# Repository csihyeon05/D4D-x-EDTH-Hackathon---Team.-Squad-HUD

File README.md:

# Squad HUD

Squad HUD is the open-source firmware, hardware and software for a real-time physiological monitoring and situational awareness system developed by **Team Squad HUD** for the **D4D × EDTH Hackathon 2026**.

The system uses **wearable sensor nodes** to collect physiological and motion data, a **NU40 wireless gateway** to receive sensor telemetry, and a **Common Operational Picture (COP)** to display the condition and location of connected personnel. A Python backend processes incoming packets, maintains individual personnel states, associates GPS coordinates with sensor IDs, and provides live information to the dashboard.

The repository holds the components of the system:

- **Soldier firmware** — Embedded firmware for wearable sensor nodes. Supports MPU6050 and NU-IMU configurations, collects sensor measurements and transmits compact telemetry advertisements. The integrated firmware uses an 18-byte packet format with an approximately 1 Hz update rate.
- **NU40 gateway** — Receives wireless advertisements from the sensor nodes and forwards telemetry to the command computer through a serial connection.
- **C2 backend** — Python service that decodes incoming packets, tracks personnel states, integrates GPS coordinates, handles missing measurements and detects communication timeouts.
- **Common Operational Picture (COP)** — An Angular web dashboard that displays physiological measurements, personnel locations, communication status and individual sensor availability.
- **Hardware** — PCB design files and embedded hardware configurations for the sensor and communication system.
- **Testing** — Automated backend tests, firmware tests, protocol compatibility checks and simulated telemetry for integration verification.

## System architecture

```text
┌───────────────────────────────┐
│      Wearable Sensor Node     │
│                               │
│  Physiological Sensors        │
│  MPU6050 / NU-IMU             │
│  Embedded Firmware            │
└───────────────┬───────────────┘
                │
        Wireless Telemetry
        18-byte Advertisement
                │
                ▼
┌───────────────────────────────┐
│          NU40 Gateway         │
│                               │
│  Wireless Packet Reception    │
│  Serial Telemetry Forwarding  │
└───────────────┬───────────────┘
                │
           Serial / USB
                │
                ▼
┌───────────────────────────────┐
│           C2 Backend          │
│                               │
│  Telemetry Decoder            │
│  Personnel State Management   │
│  GPS Association              │
│  Communication Timeout        │
└───────────────┬───────────────┘
                │
              API
                │
                ▼
┌───────────────────────────────┐
│          Squad HUD COP        │
│                               │
│  Physiological Monitoring     │
│  Personnel Location           │
│  Communication Status         │
└───────────────────────────────┘

             GPS Input
                │
                ▼
           C2 Backend
```

## Telemetry and monitoring

The monitoring system maintains a separate state for each connected sensor node. Every incoming telemetry packet is decoded by the backend and associated with the corresponding soldier ID.

The integrated sensor firmware transmits an **18-byte advertisement packet**. Its format and field definitions are documented in [`docs/DATA_SPEC.md`](./docs/DATA_SPEC.md).

The backend handles incoming measurements as follows:

1. **Sensor acquisition** — The wearable firmware collects physiological and motion measurements from the connected sensors.
2. **Wireless transmission** — The sensor node broadcasts a compact telemetry advertisement approximately once per second.
3. **Gateway reception** — The NU40 gateway receives the advertisement and forwards it to the backend through the serial interface.
4. **Packet decoding** — The backend parses the packet, extracts available measurements and associates them with the corresponding soldier ID.
5. **State update** — The latest measurements are stored in the personnel state and made available to the COP.
6. **GPS integration** — Coordinates submitted through `POST /api/gps` are associated with the specified `soldier_id`.
7. **Heart-rate availability** — The COP uses `hr_display_bpm` and `hr_status` to distinguish valid heart-rate measurements from unavailable data.
8. **Communication timeout** — In serial mode, a soldier is marked `UNKNOWN` when no telemetry has been received for more than 10 seconds. The threshold can be changed through `C2_STALE_AFTER_S`.

The dashboard obtains the latest personnel information through `/api/state`.

## Tech stack

- **Sensor firmware:** Embedded C/C++, MPU6050 and NU-IMU sensor configurations
- **Wireless communication:** NU40 development platform, wireless advertisements, serial telemetry
- **Backend:** Python, REST API, pytest
- **Frontend:** Angular, TypeScript
- **Hardware design:** PCB design files
- **Testing:** pytest, firmware test scripts, protocol parity tests and simulated telemetry

## Getting started

### C2 backend

The backend is located in `tactical-c2/backend`.

Run the automated backend tests:

```bash
cd tactical-c2/backend
python -m pytest
```

For the physical NU40 gateway, configure the backend to use serial telemetry input.

```bash
C2_SOURCE=serial
C2_SERIAL_PORT=COM10
```

`COM10` was used during the October 11, 2026 hardware integration test. Replace it with the serial port assigned to the gateway on your computer.

The communication timeout can also be configured:

```bash
C2_STALE_AFTER_S=10
```

### Common Operational Picture

The Angular frontend is located in `tactical-c2/frontend`.

Install dependencies and build the application:

```bash
cd tactical-c2/frontend
npm install
npx ng build
```

The frontend supports simulated telemetry and mock mode (`?mock`) for testing without the physical sensor network.

The dashboard reads personnel information from the backend and displays the latest available measurements, location data and communication state.

### Soldier firmware

The integrated wearable sensor firmware is located in `soldier-firmware`.

Run the firmware test suite:

```bash
cd soldier-firmware
sh tools/test.sh
```

The test suite includes protocol compatibility checks against the Python reference implementation used by the backend.

The firmware uses an 18-byte advertisement format and periodically updates its transmitted measurements.

### NU40 gateway

The gateway implementation is located in `firmware/nu40-commander`.

Run the protocol compatibility tests from the repository root:

```bash
BACKEND_ROOT=tactical-c2/backend \
sh firmware/nu40-commander/test/run.sh
```

These tests verify that telemetry vectors produced by the gateway implementation can be parsed by the backend.

For physical operation, connect the NU40 gateway to the command computer and configure the backend with the appropriate serial port.

## Project structure

```text
docs/
  DATA_SPEC.md                  Telemetry packet specification
  ...                           Protocol and validation documents

firmware/
  nucode-project/               MPU6050 sensor firmware
  nucode-project-for-nucode-imu/
                                NU-IMU sensor firmware
  nu40-commander/               NU40 gateway firmware
    test/                       Gateway compatibility tests

soldier-firmware/
  test/                         Sensor firmware and parity tests
  tools/                        Firmware testing scripts

tactical-c2/
  backend/                      Python telemetry processing and API
  frontend/                     Angular Common Operational Picture
  docs/                         Integration and hardware test records

pcb/                            Hardware design files

INTEGRATION.md                  Integration history and verification
LICENSE                         Apache License 2.0
```

## Integration and testing

The firmware, gateway, backend and frontend were developed as separate components and subsequently integrated into a single monitoring system.

The integration was verified on October 11, 2026.

| Component | Verification |
|---|---|
| C2 backend | 24 pytest tests passed |
| Angular COP | Production build successful |
| Soldier firmware | Automated tests passed |
| Protocol compatibility | 3 parity tests passed |
| NU40 gateway | Backend parser compatibility verified |
| Frontend simulation | Mock and virtual serial modes verified |
| Hardware communication | Live sensor telemetry received |

### Hardware verification

A physical NU40 gateway was connected to the command computer through `COM10`, with the backend configured to receive serial telemetry.

During the integration test, the backend successfully received live telemetry from sensor node `S1` at approximately one packet per second, including heart-rate measurements.

The frontend was also tested using simulated communication interruptions. The personnel state transitioned through live, reacquiring and `UNKNOWN` states according to the configured communication timeout.

The hardware test is documented in [`tactical-c2/docs/HW_TEST_2026-10-11.md`](./tactical-c2/docs/HW_TEST_2026-10-11.md).

## Status

The C2 backend, Angular frontend, sensor firmware tests and gateway protocol compatibility checks have passed their documented integration tests.

A physical NU40 gateway has successfully delivered live telemetry to the backend. The frontend has been verified using simulated data and virtual serial communication.

The system has **not yet been fully validated as an end-to-end multi-node deployment under field conditions**. Communication reliability, physiological measurement accuracy and behavior under extended operation require further hardware testing.

## Documentation

- [`INTEGRATION.md`](./INTEGRATION.md) — Integration history and verification results
- [`docs/DATA_SPEC.md`](./docs/DATA_SPEC.md) — Telemetry packet format and field definitions
- [`tactical-c2/docs/HW_TEST_2026-10-11.md`](./tactical-c2/docs/HW_TEST_2026-10-11.md) — Hardware integration test

## License

Licensed under the [Apache License 2.0](./LICENSE).

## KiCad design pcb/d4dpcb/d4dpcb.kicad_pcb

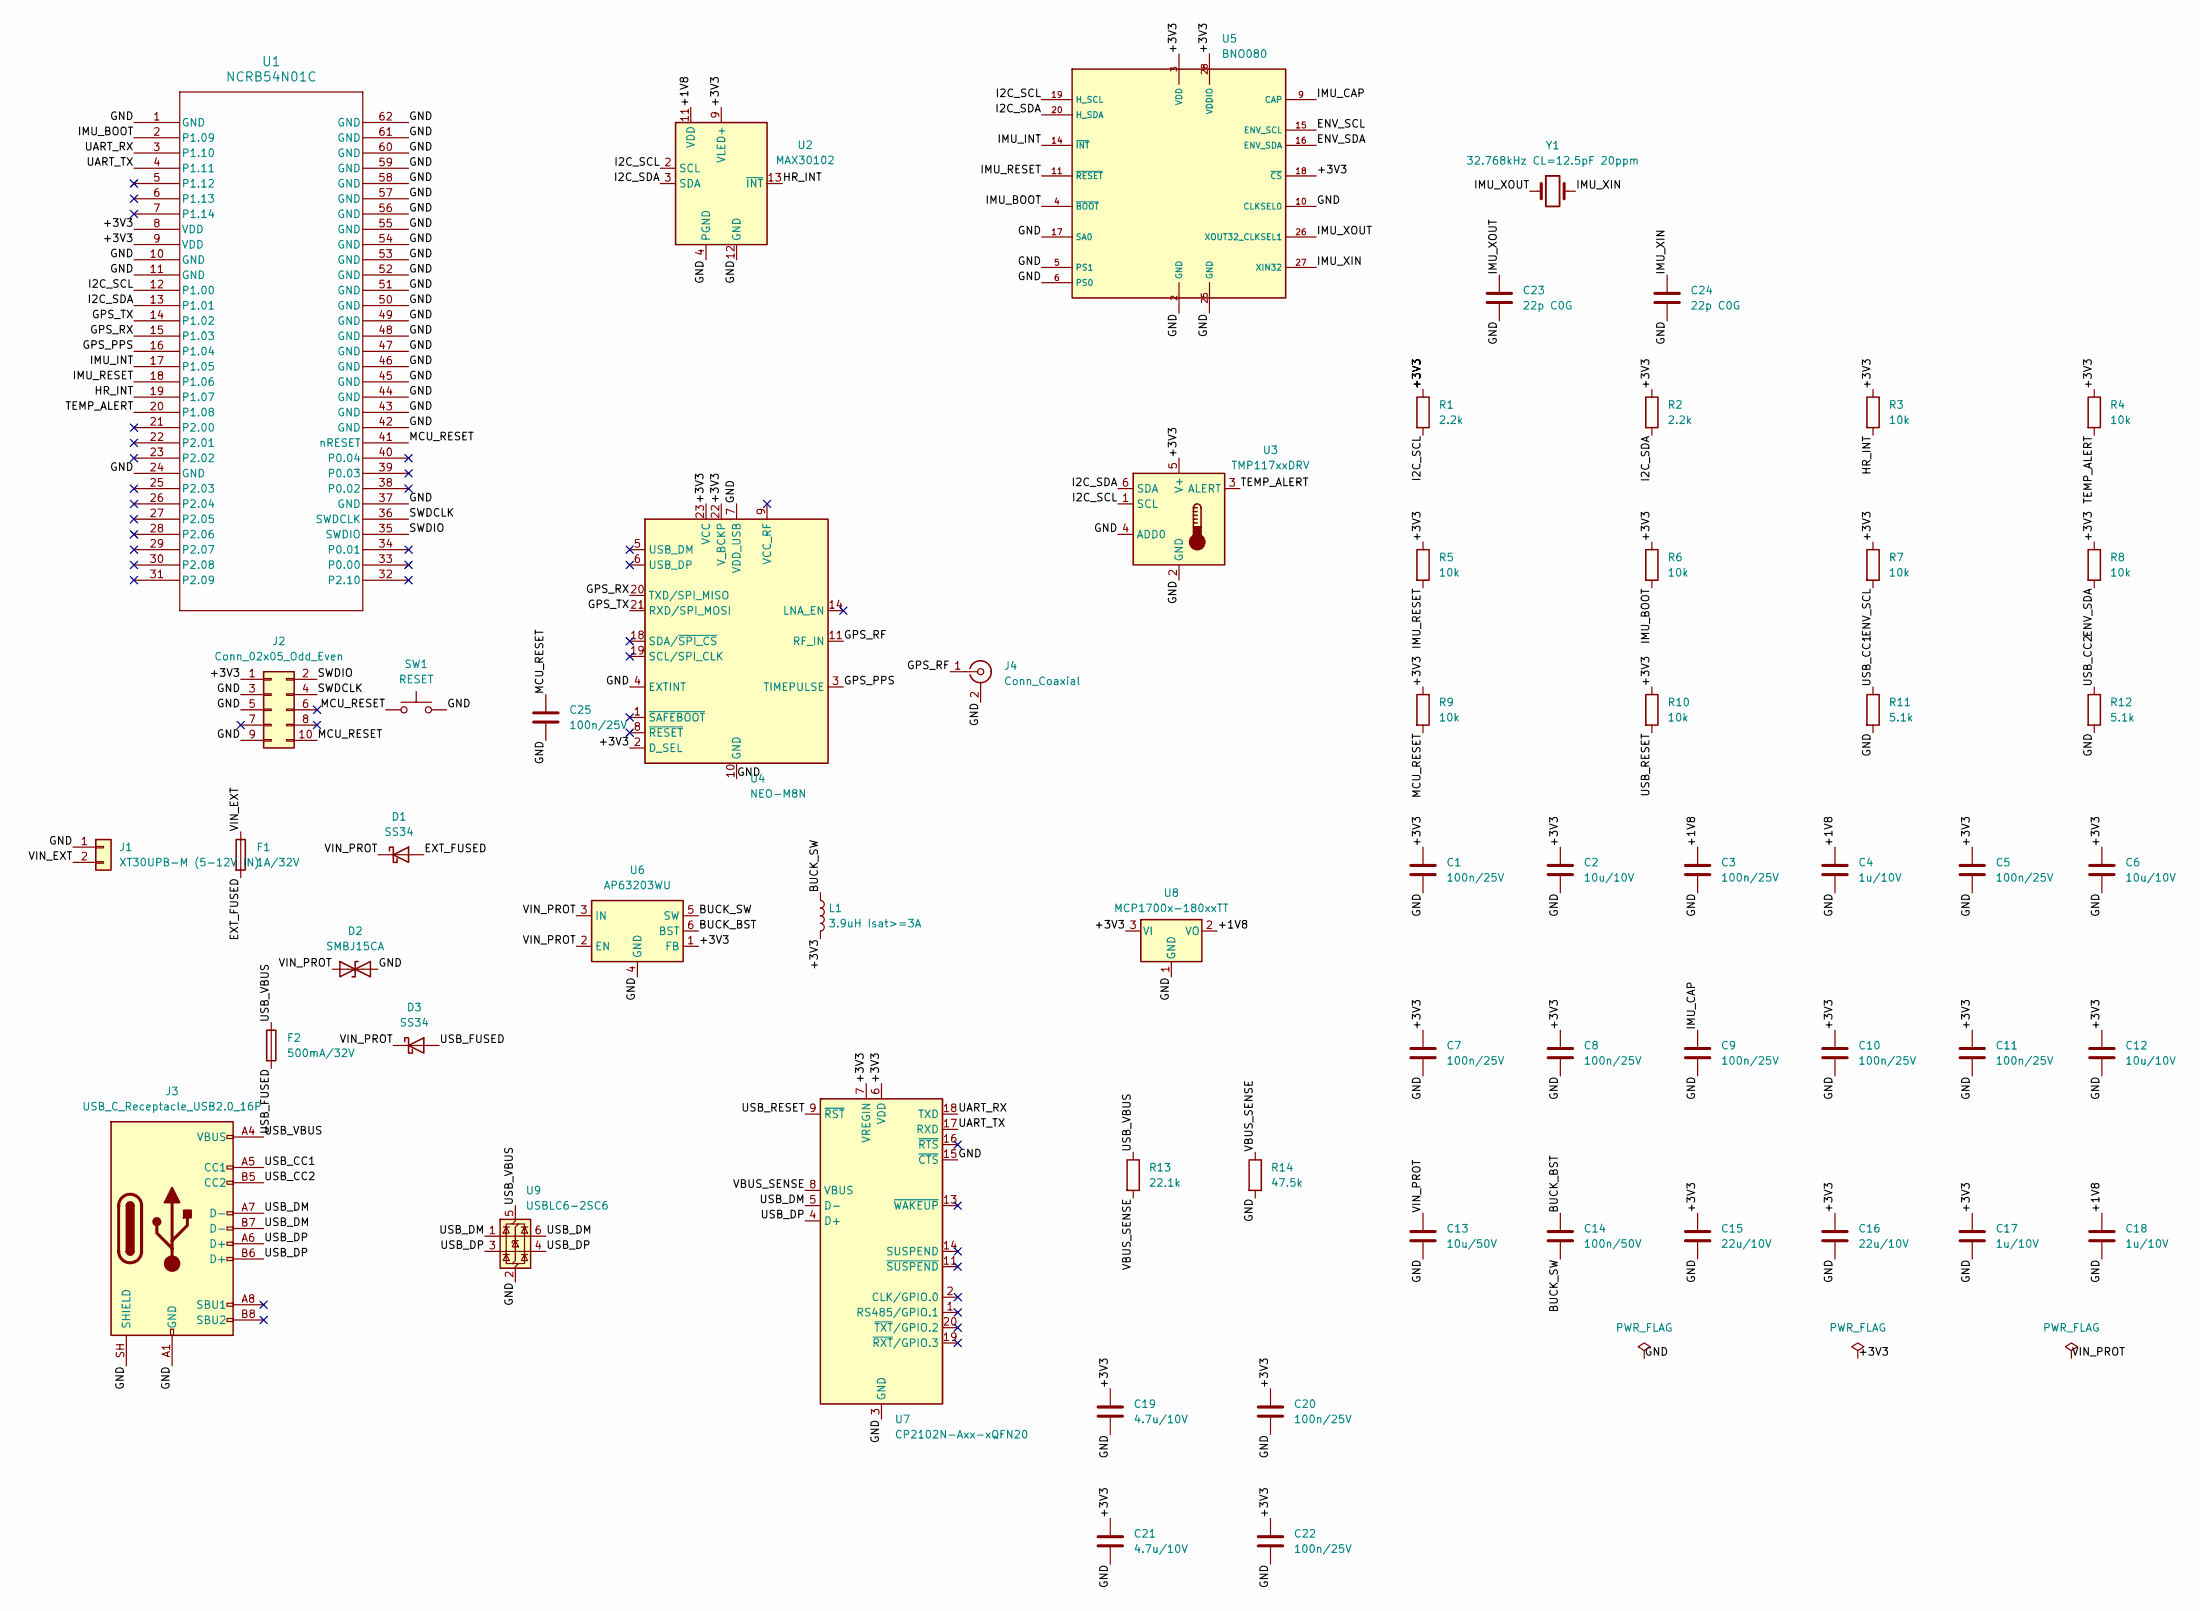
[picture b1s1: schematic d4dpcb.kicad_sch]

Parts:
C1, C3, C5, C7, C8, C9, C10, C11, C20, C22, C25: 100n/25V; C_0603_1608Metric
C2, C6, C12: 10u/10V; C_0805_2012Metric
C4, C17, C18: 1u/10V; C_0603_1608Metric
C13: 10u/50V; C_1210_3225Metric
C14: 100n/50V; C_0603_1608Metric
C15, C16: 22u/10V; C_1206_3216Metric
C19, C21: 4.7u/10V; C_0603_1608Metric
C23, C24: 22p C0G; C_0603_1608Metric
D1, D3: SS34; D_SMA
D2: SMBJ15CA; D_SMB
F1: 1A/32V; Fuse_1206_3216Metric
F2: 500mA/32V; Fuse_1206_3216Metric
J1: XT30UPB-M (5-12V IN); AMASS_XT30UPB-M_1x02_P5.0mm_Vertical
J2: Conn_02x05_Odd_Even; PinHeader_2x05_P1.27mm_Vertical
J3: USB_C_Receptacle_USB2.0_16P; USB_C_Receptacle_GCT_USB4105-xx-A_16P_TopMnt_Horizontal
J4: Conn_Coaxial; U.FL_Hirose_U.FL-R-SMT-1_Vertical
L1: 3.9uH Isat>=3A; L_Bourns-SRN6028
R1, R2: 2.2k; R_0603_1608Metric
R3, R4, R5, R6, R7, R8, R9, R10: 10k; R_0603_1608Metric
R11, R12: 5.1k; R_0603_1608Metric
R13: 22.1k; R_0603_1608Metric
R14: 47.5k; R_0603_1608Metric
SW1: RESET; SW_SPST_B3U-1000P
U1: NCRB54N01C; MODULE_NU-54_NUC
U2: MAX30102; Maxim_OLGA-14_3.3x5.6mm_P0.8mm
U3: TMP117xxDRV; WSON-6-1EP_2x2mm_P0.65mm_EP1x1.6mm
U4: NEO-M8N; ublox_NEO
U5: BNO080; LGA-28_5.2x3.8mm_P0.5mm
U6: AP63203WU; TSOT-23-6
U7: CP2102N-Axx-xQFN20; SiliconLabs_QFN-20-1EP_3x3mm_P0.5mm_EP1.8x1.8mm
U8: MCP1700x-180xxTT; SOT-23
U9: USBLC6-2SC6; SOT-23-6
Y1: 32.768kHz CL=12.5pF 20ppm; Crystal_SMD_3215-2Pin_3.2x1.5mm

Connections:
/+1V8: C3.1, C4.1, C18.1, U2.11 (VDD), U8.2 (VO)
/+3V3: C1.1, C2.1, C5.1, C6.1, C7.1, C8.1, C10.1, C11.1, C12.1, C15.1, C16.1, C17.1, C19.1, C20.1, C21.1, C22.1, J2.1, L1.2, R1.1, R2.1, R3.1, R4.1, R5.1, R6.1, R7.1, R8.1, R9.1, R10.1, U1.8 (VDD), U1.9 (VDD), U2.9 (VLED+), U2.10 (VLED+), U3.5 (V+), U4.2 (D_SEL), U4.22 (V_BCKP), U4.23 (VCC), U5.3 (VDD), U5.18 (~CS), U5.28 (VDDIO), U6.1 (FB), U7.6 (VDD), U7.7 (VREGIN), U8.3 (VI)
/BUCK_BST: C14.1, U6.6 (BST)
/BUCK_SW: C14.2, L1.1, U6.5 (SW)
/ENV_SCL: R7.2, U5.15 (ENV_SCL)
/ENV_SDA: R8.2, U5.16 (ENV_SDA)
/EXT_FUSED: D1.2 (A), F1.2
/GND: C1.2, C2.2, C3.2, C4.2, C5.2, C6.2, C7.2, C8.2, C9.2, C10.2, C11.2, C12.2, C13.2, C15.2, C16.2, C17.2, C18.2, C19.2, C20.2, C21.2, C22.2, C23.2, C24.2, C25.2, D2.2 (A2), J1.1, J2.3, J2.5, J2.9, J3.A1 (GND), J3.A12 (GND), J3.B1 (GND), J3.B12 (GND), J3.SH (SHIELD), J4.2 (Ext), R11.2, R12.2, R14.2, SW1.2, U1.1 (GND), U1.10 (GND), U1.11 (GND), U1.24 (GND), U1.37 (GND), U1.42 (GND), U1.43 (GND), U1.44 (GND), U1.45 (GND), U1.46 (GND), U1.47 (GND), U1.48 (GND), U1.49 (GND), U1.50 (GND), U1.51 (GND), U1.52 (GND), U1.53 (GND), U1.54 (GND), U1.55 (GND), U1.56 (GND), U1.57 (GND), U1.58 (GND), U1.59 (GND), U1.60 (GND), U1.61 (GND), U1.62 (GND), U2.4 (PGND), U2.12 (GND), U3.2 (GND), U3.4 (ADD0), U4.4 (EXTINT), U4.7 (VDD_USB), U4.10 (GND), U4.12 (GND), U4.13 (GND), U4.24 (GND), U5.2 (GND), U5.5 (PS1), U5.6 (PS0), U5.10 (CLKSEL0), U5.17 (SA0), U5.25 (GND), U6.4 (GND), U7.3 (GND), U7.12 (GND), U7.15 (~CTS), U7.21 (GND), U8.1 (GND), U9.2 (GND)
/GPS_PPS: U1.16 (P1.04), U4.3 (TIMEPULSE)
/GPS_RF: J4.1 (In), U4.11 (RF_IN)
/GPS_RX: U1.15 (P1.03), U4.20 (TXD/SPI_MISO)
/GPS_TX: U1.14 (P1.02), U4.21 (RXD/SPI_MOSI)
/HR_INT: R3.2, U1.19 (P1.07), U2.13 (~INT)
/I2C_SCL: R1.2, U1.12 (P1.00), U2.2 (SCL), U3.1 (SCL), U5.19 (H_SCL)
/I2C_SDA: R2.2, U1.13 (P1.01), U2.3 (SDA), U3.6 (SDA), U5.20 (H_SDA)
/IMU_BOOT: R6.2, U1.2 (P1.09), U5.4 (~BOOT)
/IMU_CAP: C9.1, U5.9 (CAP)
/IMU_INT: U1.17 (P1.05), U5.14 (~INT)
/IMU_RESET: R5.2, U1.18 (P1.06), U5.11 (~RESET)
/IMU_XIN: C24.1, U5.27 (XIN32), Y1.2
/IMU_XOUT: C23.1, U5.26 (XOUT32_CLKSEL1), Y1.1
/MCU_RESET: C25.1, J2.10, R9.2, SW1.1, U1.41 (nRESET)
/SWDCLK: J2.4, U1.36 (SWDCLK)
/SWDIO: J2.2, U1.35 (SWDIO)
/TEMP_ALERT: R4.2, U1.20 (P1.08), U3.3 (ALERT)
/UART_RX: U1.3 (P1.10), U7.18 (TXD)
/UART_TX: U1.4 (P1.11), U7.17 (RXD)
/USB_CC1: J3.A5 (CC1), R11.1
/USB_CC2: J3.B5 (CC2), R12.1
/USB_DM: J3.A7 (D-), J3.B7 (D-), U7.5 (D-), U9.1 (I/O1), U9.6 (I/O1)
/USB_DP: J3.A6 (D+), J3.B6 (D+), U7.4 (D+), U9.3 (I/O2), U9.4 (I/O2)
/USB_FUSED: D3.2 (A), F2.2
/USB_RESET: R10.2, U7.9 (~RST)
/USB_VBUS: F2.1, J3.A4 (VBUS), J3.A9 (VBUS), J3.B4 (VBUS), J3.B9 (VBUS), R13.1, U9.5 (VBUS)
/VBUS_SENSE: R13.2, R14.1, U7.8 (VBUS)
/VIN_EXT: F1.1, J1.2
/VIN_PROT: C13.1, D1.1 (K), D2.1 (A1), D3.1 (K), U6.2 (EN), U6.3 (IN)

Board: 2 copper layers, 60 parts (0 on the bottom side), 37 nets, no tracks yet.

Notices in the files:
README.md:
License: Apache 2.0
